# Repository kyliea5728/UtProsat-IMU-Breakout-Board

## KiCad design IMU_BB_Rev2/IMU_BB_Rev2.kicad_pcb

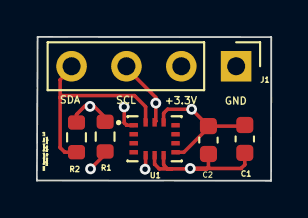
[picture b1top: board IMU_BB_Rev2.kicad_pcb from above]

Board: 4 copper layers, 13.0 x 8.0 mm, 6 parts (0 on the bottom side), 4 nets.

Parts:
C1, C2: 100nF; C_0603_1608Metric
J1: Conn_01x04; PinHeader_1x04_P3.00mm_Vertical
R1, R2: 10K; R_0603_1608Metric
U1: BMI270; XDCR_BMI270

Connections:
+3V3: C1.2, C2.2, J1.2, R1.2, R2.2, U1.5 (VDDIO), U1.8 (VDD), U1.12 (CSB)
/IMU_A_SCL: J1.3, R1.1, U1.13 (SCX)
/IMU_A_SDA: J1.4, R2.1, U1.14 (SDX)
GND: C1.1, C2.1, J1.1, U1.1 (SDO), U1.6 (GNDIO), U1.7 (GND)

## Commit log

2022-03-15 Add files via upload
    Schematic done. Haven't added footprints.
2022-03-15 Add files via upload
    Used 1x6 connector.
2022-03-16 stretched top ground plane
2022-03-16 final commit 3/16
2022-03-17 Revision 2 Start
2022-03-18 3/17
2022-03-18 3/18 Needs checking
2022-03-19 3/19
2022-03-19 final commit
